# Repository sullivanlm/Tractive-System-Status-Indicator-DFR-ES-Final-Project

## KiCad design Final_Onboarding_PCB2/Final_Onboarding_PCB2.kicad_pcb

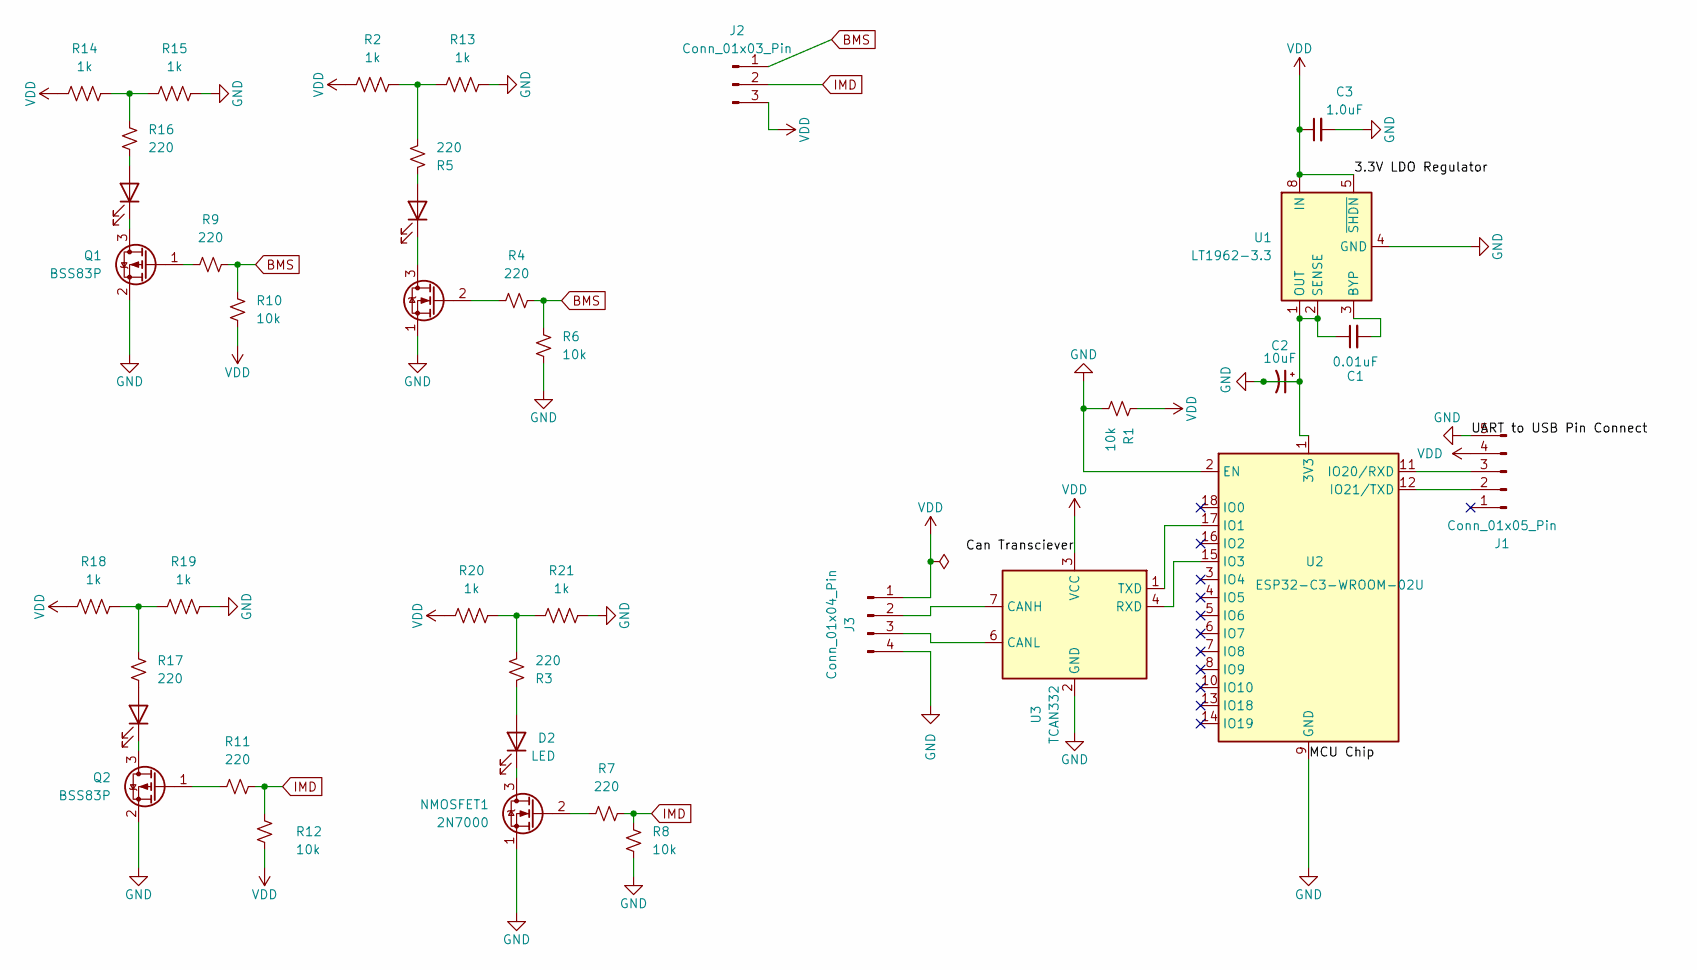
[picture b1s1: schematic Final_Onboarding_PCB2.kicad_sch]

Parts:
C1: 0.01uF; C_0402_1005Metric; Voltage 16V; Tolerance 10%
C2: 10uF; CP_Axial_L11.0mm_D5.0mm_P18.00mm_Horizontal; Voltage 100V; Tolerance 20%
C3: 1.0uF; C_0603_1608Metric; Voltage 16V; Tolerance 10%
D2, D3, D6, D7: LED; LED_D3.0mm
J1: Conn_01x05_Pin; SolderWire-0.1sqmm_1x05_P3.6mm_D0.4mm_OD1mm
J2: Conn_01x03_Pin; SolderWire-0.1sqmm_1x03_P3.6mm_D0.4mm_OD1mm
J3: Conn_01x04_Pin; SolderWire-0.1sqmm_1x04_P3.6mm_D0.4mm_OD1mm
NMOSFET1, NMOSFET2: 2N7000; TO-92_Inline
Q1, Q2: BSS83P; SOT-23
R1: 10k; R_0603_1608Metric
R2, R13, R14, R15, R18, R19, R20, R21: 1k; R_0603_1608Metric
R3, R4, R5, R7, R9, R11, R16, R17: 220; R_0402_1005Metric
R6, R8, R10, R12: 10k; R_0402_1005Metric
U1: LT1962-3.3; MSOP-8_3x3mm_P0.65mm
U2: ESP32-C3-WROOM-02U
U3: TCAN332; SOIC-8_3.9x4.9mm_P1.27mm

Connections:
BMS: J2.1, R4.1, R6.2, R9.1, R10.2
GND: C1.1, C2.1, C2.2, C3.2, J1.5, J3.4, NMOSFET1.1 (S), NMOSFET2.1 (S), Q1.2 (S), Q2.2 (S), R1.2, R6.1, R8.1, R13.1, R15.1, R19.1, R21.1, U1.1 (OUT), U1.2 (SENSE), U1.4 (GND), U2.1 (3V3), U2.2 (EN), U2.9 (GND), U2.19 (GND), U3.2 (GND)
IMD: J2.2, R7.1, R8.2, R11.1, R12.2
unnamed: D2.2 (A), R3.1
unnamed: D2.1 (K), NMOSFET1.3 (D)
unnamed: D3.2 (A), R5.1
unnamed: D3.1 (K), NMOSFET2.3 (D)
unnamed: D6.2 (A), R16.2
unnamed: D6.1 (K), Q1.3 (D)
unnamed: D7.2 (A), R17.2
unnamed: D7.1 (K), Q2.3 (D)
unnamed: J1.2, U2.12 (IO21/TXD)
unnamed: J1.3, U2.11 (IO20/RXD)
unnamed: J3.2, U3.7 (CANH)
unnamed: J3.3, U3.6 (CANL)
unnamed: NMOSFET1.2 (G), R7.2
unnamed: NMOSFET2.2 (G), R4.2
unnamed: Q1.1 (G), R9.2
unnamed: Q2.1 (G), R11.2
unnamed: R2.1, R5.2, R13.2
unnamed: R14.1, R15.2, R16.1
unnamed: R17.1, R18.1, R19.2
unnamed: R3.2, R20.1, R21.2
unnamed: C1.2, U1.3 (BYP)
unnamed: U2.17 (IO1), U3.1 (TXD)
unnamed: U2.15 (IO3), U3.4 (RXD)
VDD: C3.1, J1.4, J2.3, J3.1, R1.1, R2.2, R10.1, R12.1, R14.2, R18.2, R20.2, U1.5 (~SHDN), U1.8 (IN), U3.3 (VCC)

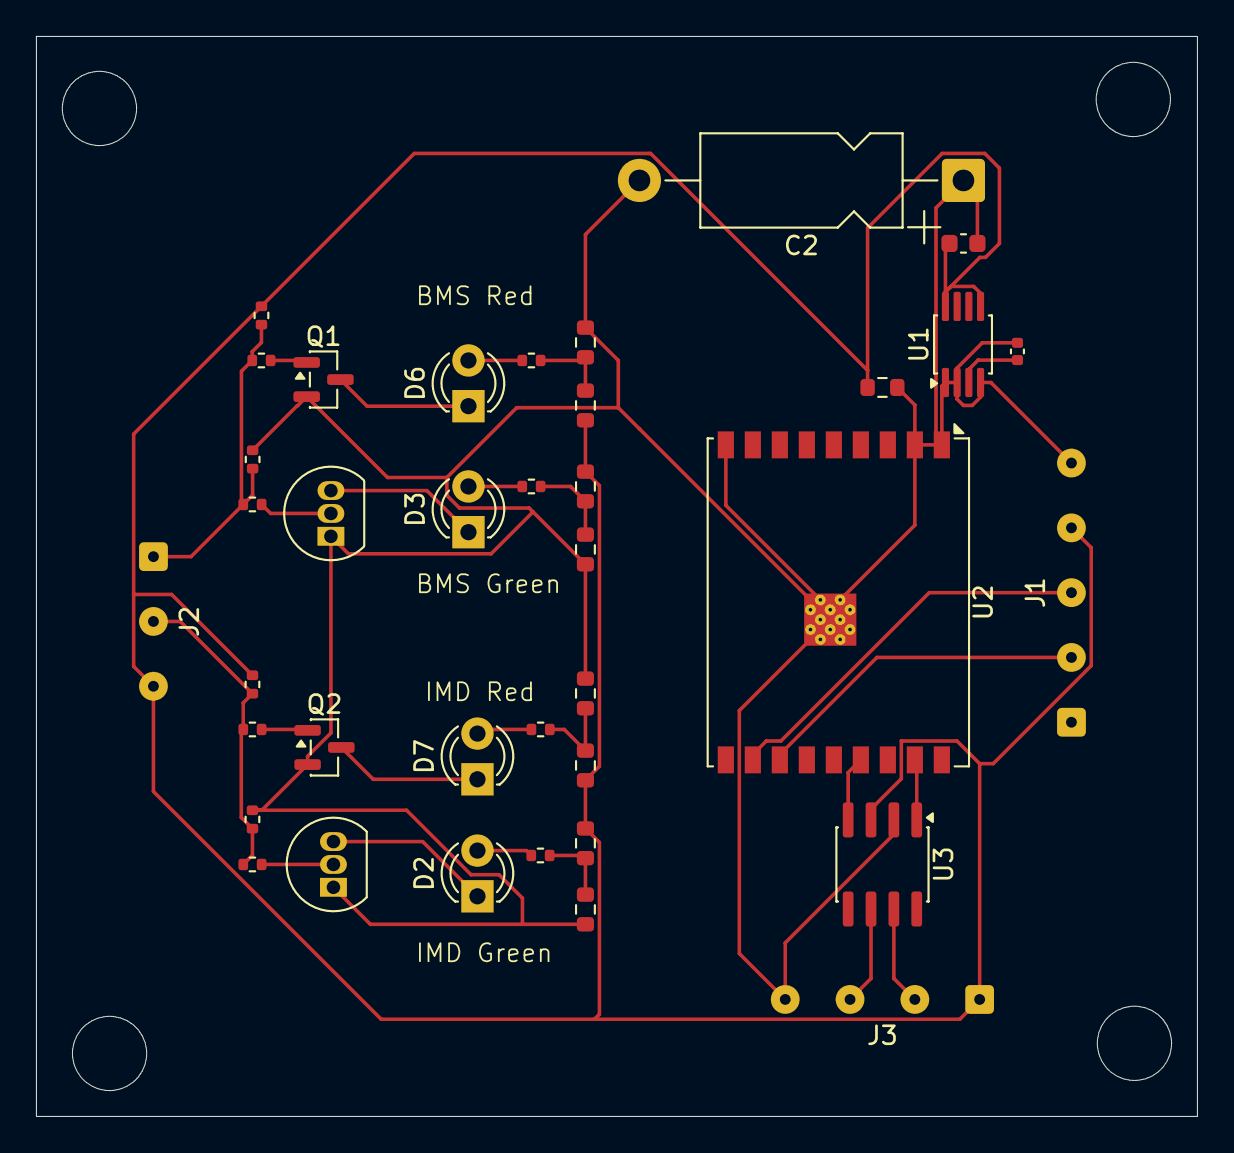
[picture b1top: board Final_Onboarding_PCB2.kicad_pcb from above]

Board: 2 copper layers, 64.5 x 60.0 mm, 38 parts (0 on the bottom side), 27 nets.
